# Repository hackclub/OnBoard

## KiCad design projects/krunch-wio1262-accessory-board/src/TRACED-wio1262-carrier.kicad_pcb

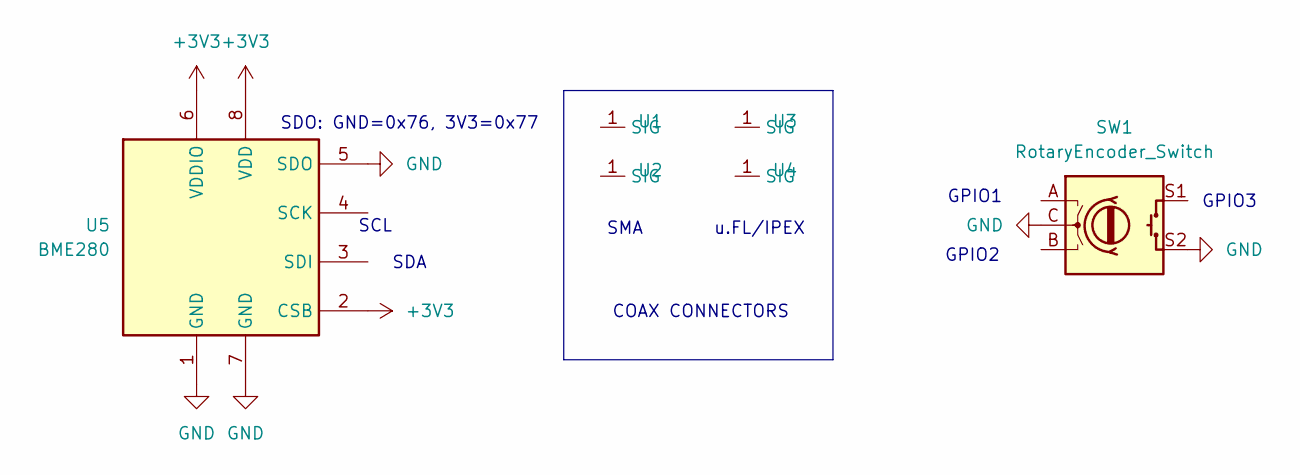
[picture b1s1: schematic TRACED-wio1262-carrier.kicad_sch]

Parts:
SW1: RotaryEncoder_Switch; RotaryEncoder_Alps_EC11E-Switch_Vertical_H20mm
U1, U2: SMA_BAT_Wireless_BWSMA-KWE-Z001; LCSC Part # C20617216
U3, U4: U.FL_Molex_MCRF_73412-0110_Vertical; LCSC Part # C434812
U5: BME280; Bosch_LGA-8_2.5x2.5mm_P0.65mm_ClockwisePinNumbering

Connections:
+3V3: U5.2 (CSB), U5.6 (VDDIO), U5.8 (VDD)
GND: SW1.C, SW1.S2, U5.1 (GND), U5.5 (SDO), U5.7 (GND)
GPIO1: SW1.A
GPIO2: SW1.B
GPIO3: SW1.S1
GPIO5/SDA: U5.3 (SDI)
GPIO6/SCL: U5.4 (SCK)

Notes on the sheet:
GPIO1
GPIO2
SMA
SCL
u.FL/IPEX
SDA
SDO: GND=0x76, 3V3=0x77
GPIO3
COAX CONNECTORS

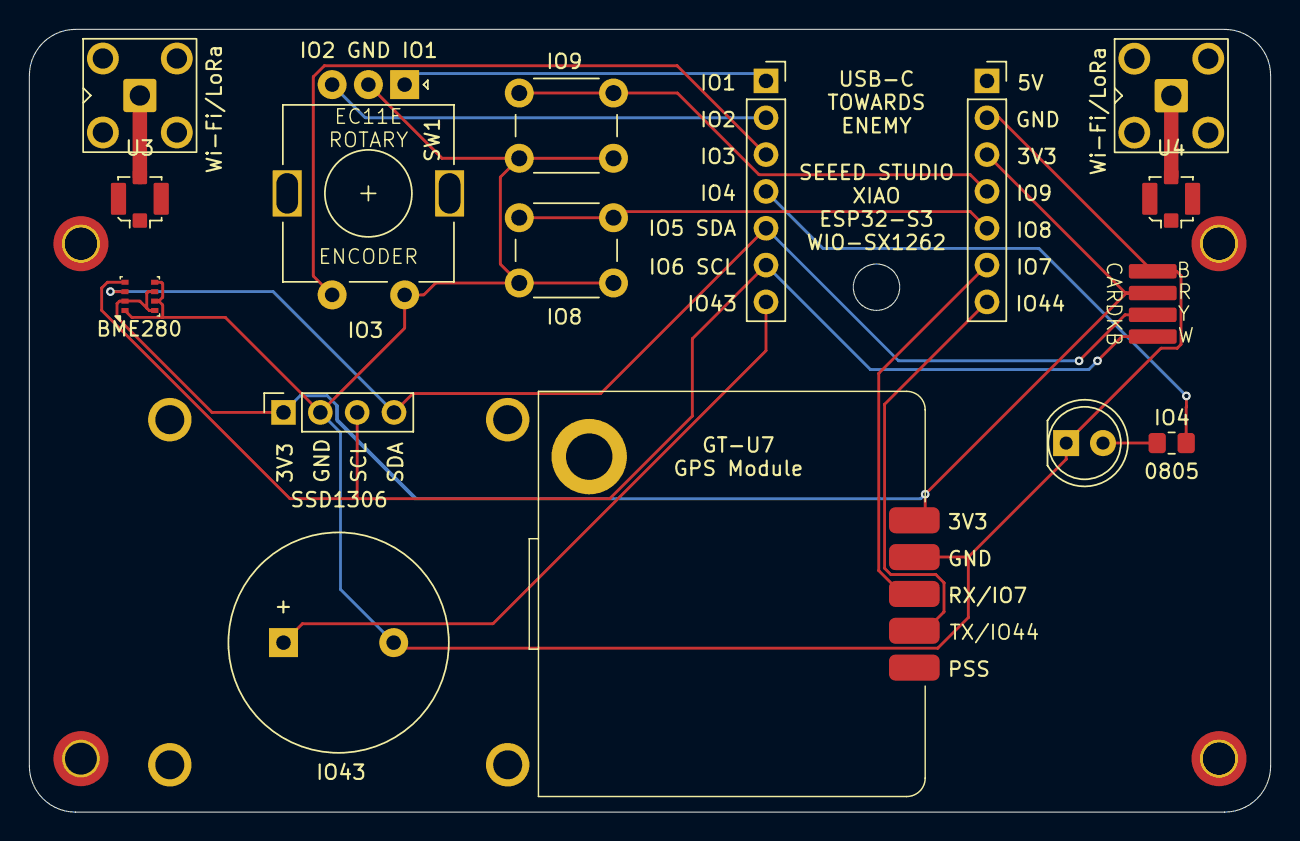
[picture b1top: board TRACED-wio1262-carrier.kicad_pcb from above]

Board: 2 copper layers, 85.6 x 54.0 mm, 6 parts (0 on the bottom side), 2 nets.

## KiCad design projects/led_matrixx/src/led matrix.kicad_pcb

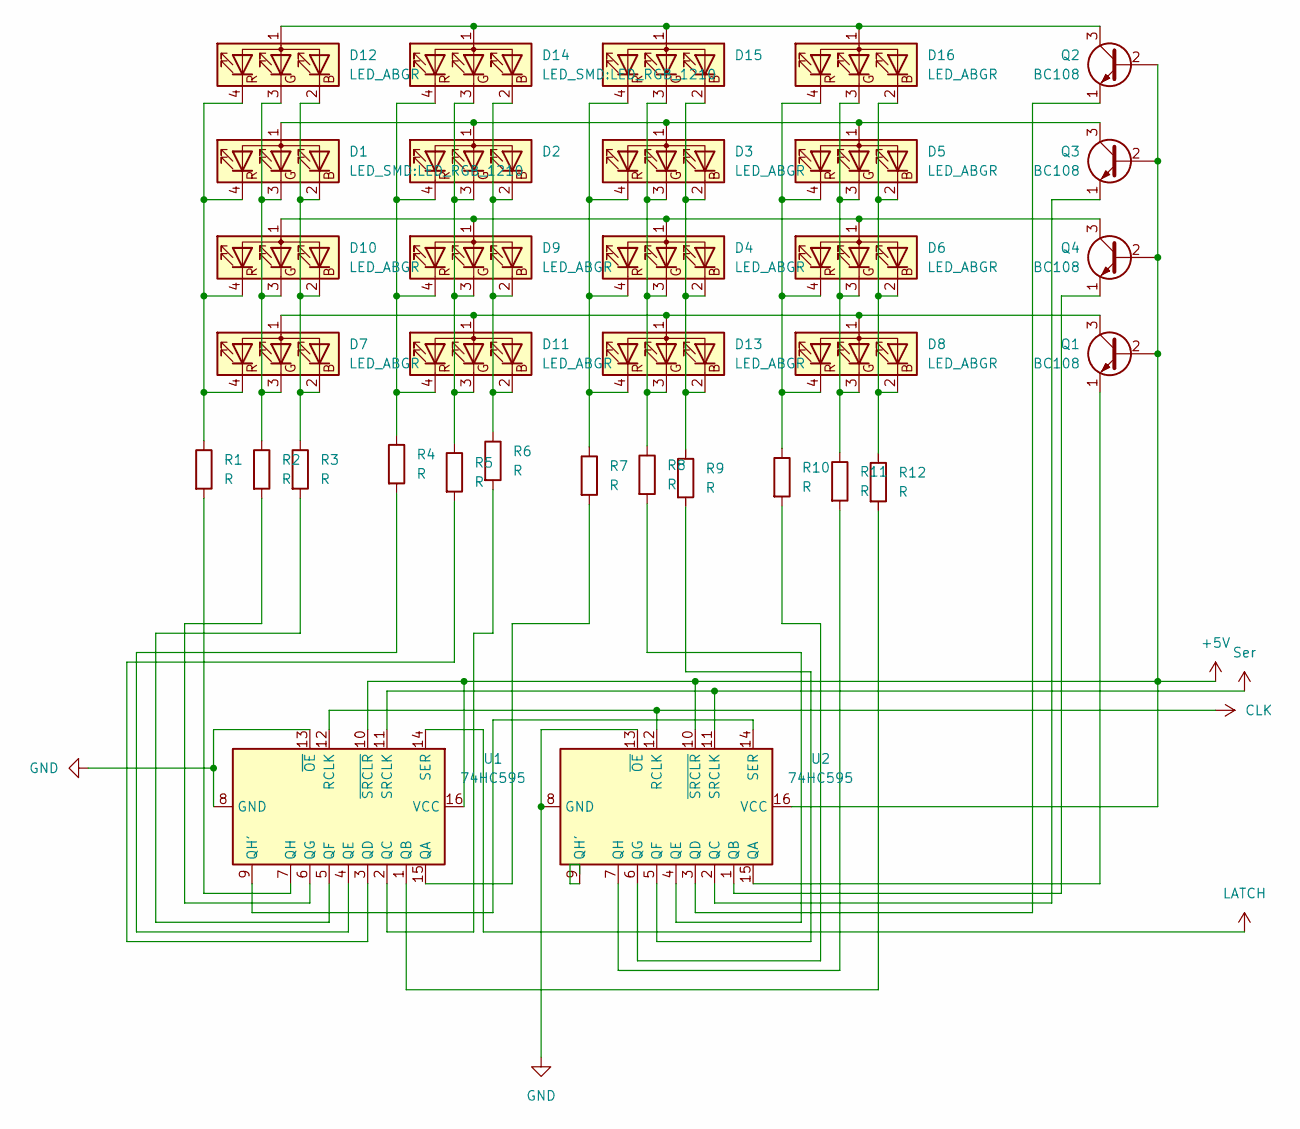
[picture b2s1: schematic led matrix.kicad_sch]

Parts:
D1, D14: LED_SMD:LED_RGB_1210; LED_RGB_1210
D2, D3, D4, D5, D6, D7, D8, D9, D10, D11, D12, D13, D15, D16: LED_ABGR; LED_RGB_1210
Q1, Q2, Q3, Q4: BC108; TO-18-3
R1, R2, R3, R4, R5, R6, R7, R8, R9, R10, R11, R12: R; R_0201_0603Metric
U1, U2: 74HC595; SSOP-16_5.3x6.2mm_P0.65mm

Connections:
+5V: Q1.2 (B), Q2.2 (B), Q3.2 (B), Q4.2 (B), U1.10 (~SRCLR), U1.16 (VCC), U2.10 (~SRCLR), U2.16 (VCC)
CLK: U1.12 (RCLK), U2.12 (RCLK)
GND: U1.8 (GND), U1.13 (~OE), U2.8 (GND), U2.13 (~OE)
LATCH: U1.14 (SER)
unnamed: D1.1 (A), D2.1 (A), D3.1 (A), D5.1 (A), Q3.3 (C)
unnamed: D1.2 (BK), D7.2 (BK), D10.2 (BK), D12.2 (BK), R3.1
unnamed: D1.3 (GK), D7.3 (GK), D10.3 (GK), D12.3 (GK), R2.1
unnamed: D1.4 (RK), D7.4 (RK), D10.4 (RK), D12.4 (RK), R1.1
unnamed: D4.1 (A), D6.1 (A), D9.1 (A), D10.1 (A), Q4.3 (C)
unnamed: D7.1 (A), D8.1 (A), D11.1 (A), D13.1 (A), Q1.3 (C)
unnamed: D2.2 (BK), D9.2 (BK), D11.2 (BK), D14.2 (BK), R6.1
unnamed: D2.3 (GK), D9.3 (GK), D11.3 (GK), D14.3 (GK), R5.1
unnamed: D2.4 (RK), D9.4 (RK), D11.4 (RK), D14.4 (RK), R4.1
unnamed: D12.1 (A), D14.1 (A), D15.1 (A), D16.1 (A), Q2.3 (C)
unnamed: D3.2 (BK), D4.2 (BK), D13.2 (BK), D15.2 (BK), R9.1
unnamed: D3.3 (GK), D4.3 (GK), D13.3 (GK), D15.3 (GK), R8.1
unnamed: D3.4 (RK), D4.4 (RK), D13.4 (RK), D15.4 (RK), R7.1
unnamed: D5.2 (BK), D6.2 (BK), D8.2 (BK), D16.2 (BK), R12.1
unnamed: D5.3 (GK), D6.3 (GK), D8.3 (GK), D16.3 (GK), R11.1
unnamed: D5.4 (RK), D6.4 (RK), D8.4 (RK), D16.4 (RK), R10.1
unnamed: Q1.1 (E), U2.15 (QA)
unnamed: Q2.1 (E), U2.3 (QD)
unnamed: Q3.1 (E), U2.2 (QC)
unnamed: Q4.1 (E), U2.1 (QB)
unnamed: R7.2, U1.15 (QA)
unnamed: R12.2, U1.1 (QB)
unnamed: R6.2, U1.2 (QC)
unnamed: R5.2, U1.3 (QD)
unnamed: R4.2, U1.4 (QE)
unnamed: R3.2, U1.5 (QF)
unnamed: R2.2, U1.6 (QG)
unnamed: U1.9 (QH'), U2.14 (SER)
unnamed: R1.2, U1.7 (QH)
unnamed: R8.2, U2.4 (QE)
unnamed: R9.2, U2.5 (QF)
unnamed: R10.2, U2.6 (QG)
unnamed: R11.2, U2.7 (QH)
Ser: U1.11 (SRCLK), U2.11 (SRCLK)

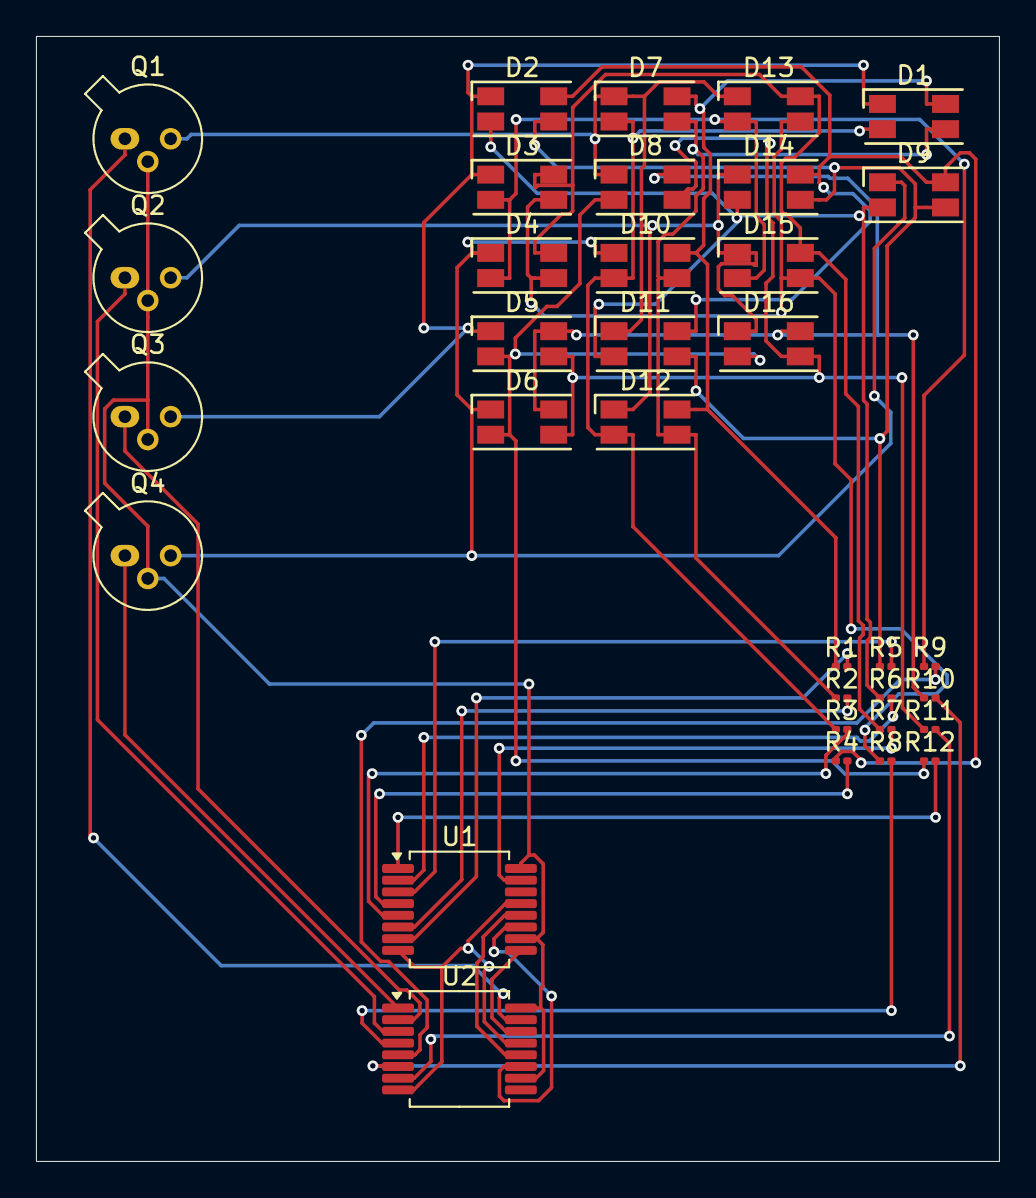
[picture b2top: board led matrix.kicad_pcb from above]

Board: 2 copper layers, 53.5 x 62.5 mm, 34 parts (0 on the bottom side), 37 nets.

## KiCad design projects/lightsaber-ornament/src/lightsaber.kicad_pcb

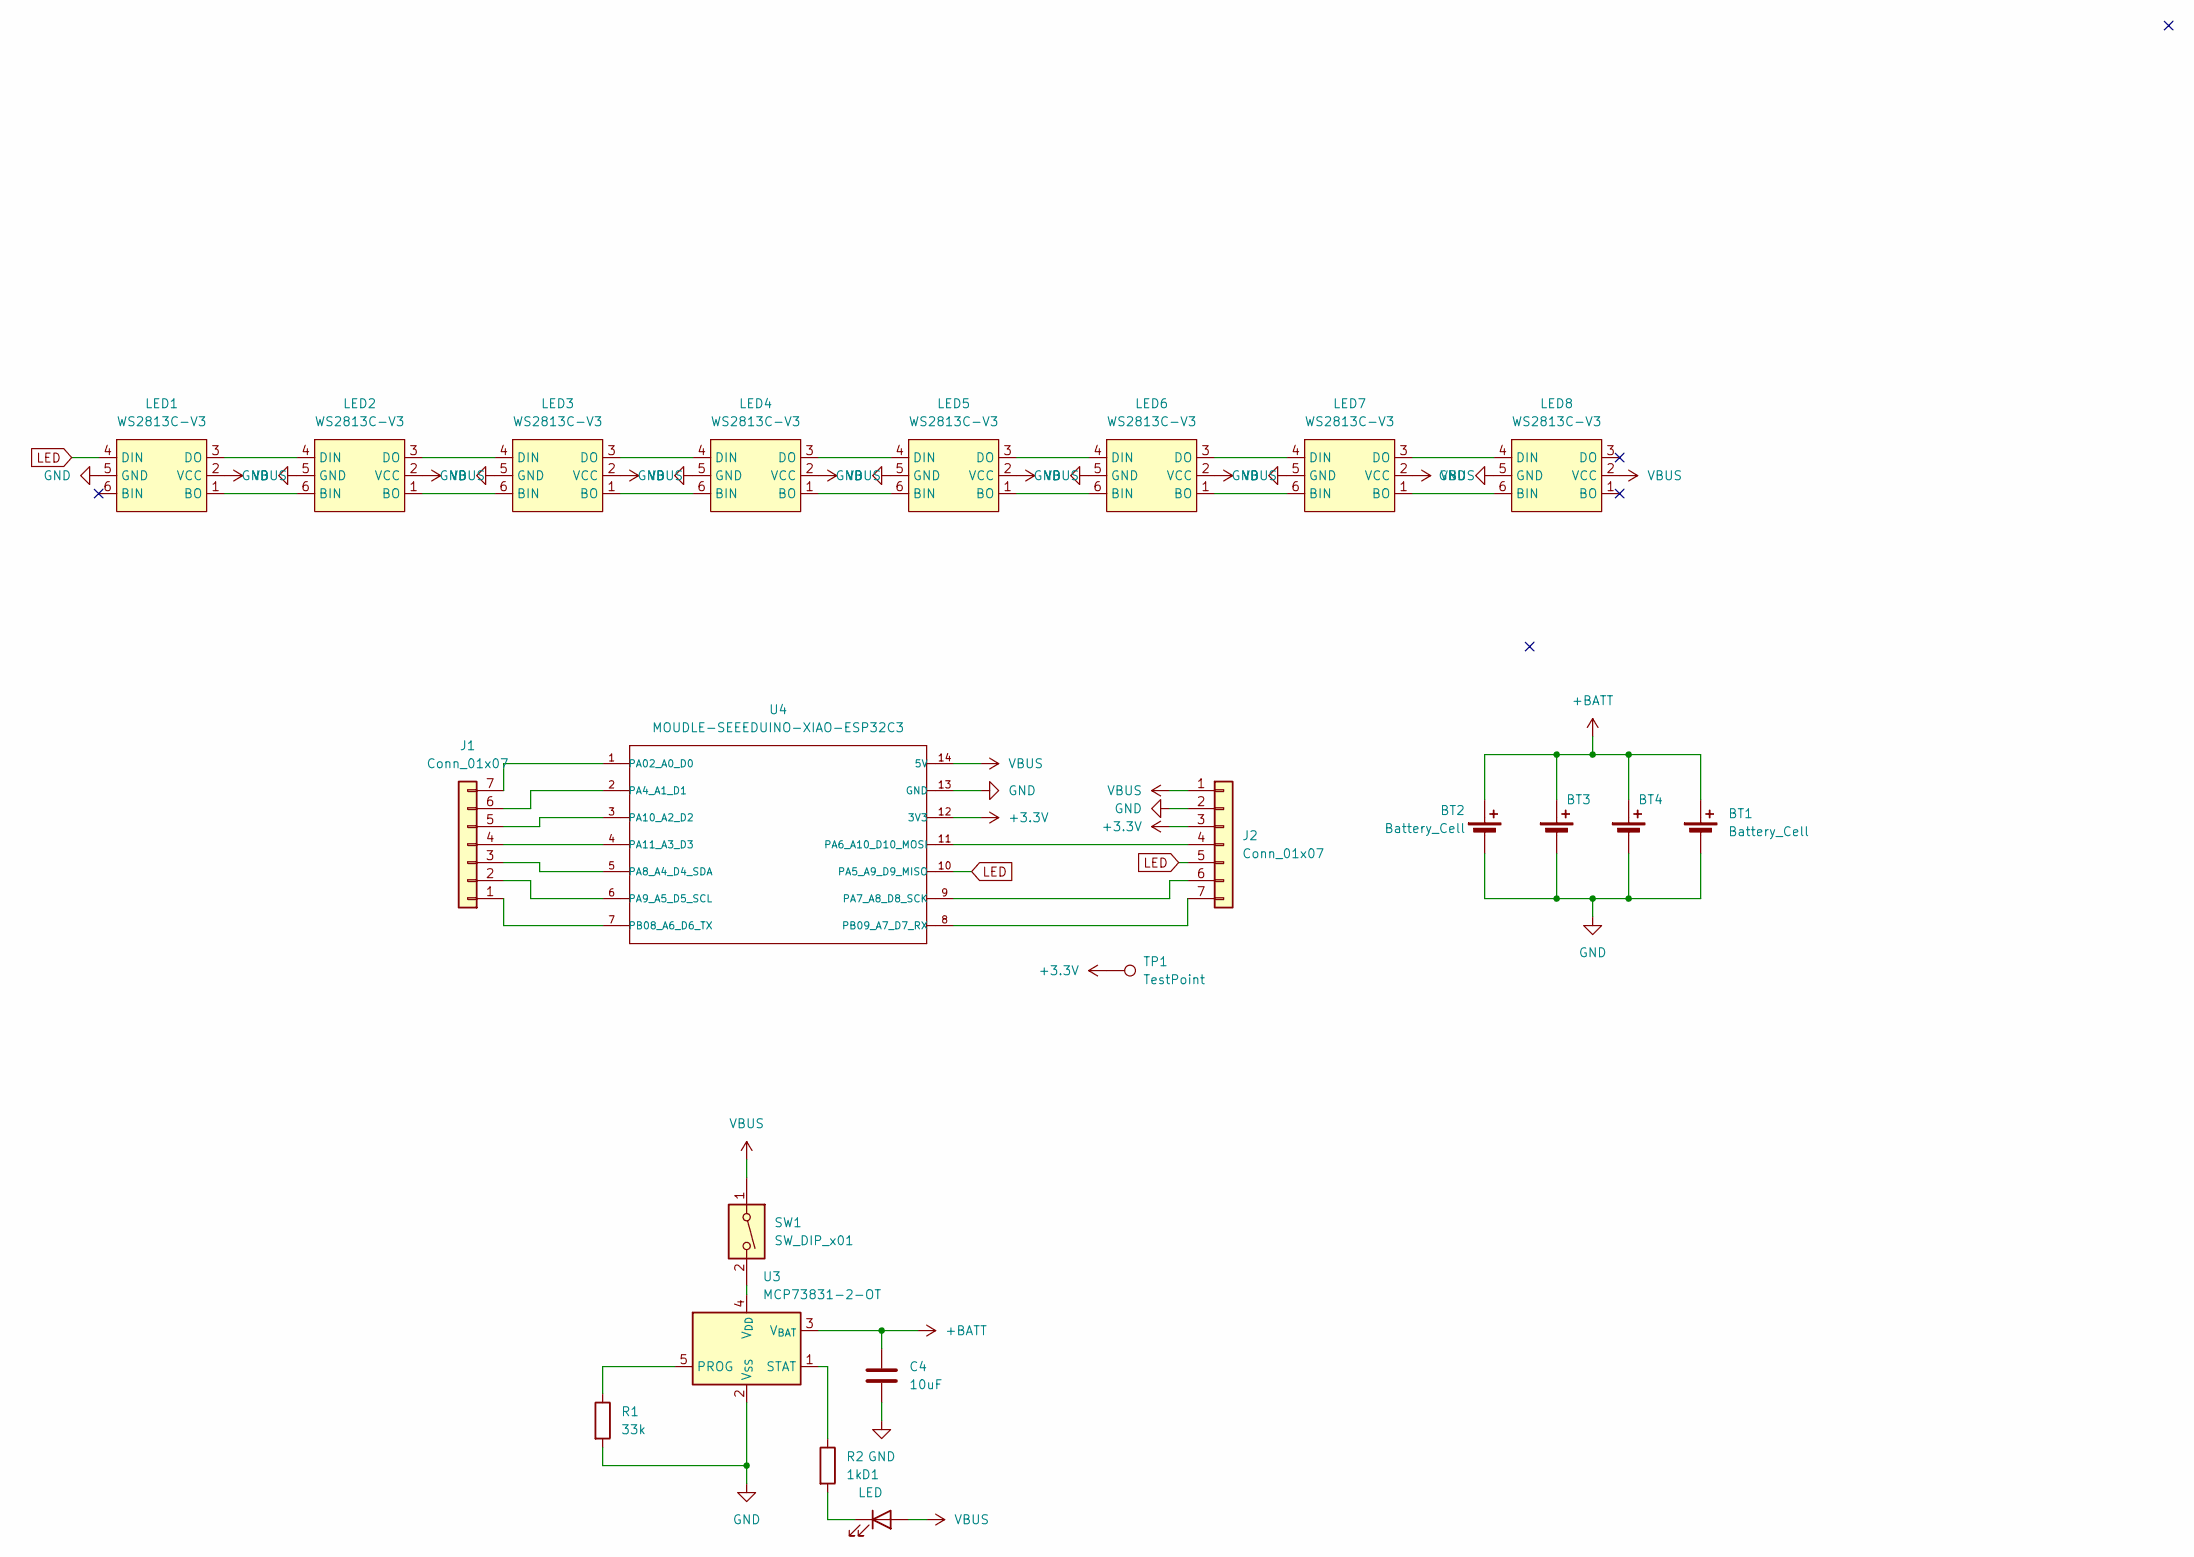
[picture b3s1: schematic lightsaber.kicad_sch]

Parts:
BT1, BT2, BT3, BT4: Battery_Cell; Battery_Panasonic_CR2032-HFN_Horizontal_CircularHoles
C4: 10uF; CAP_FA23_TDK
D1: LED; LED_D3.0mm_Clear
J1, J2: Conn_01x07; PinSocket_1x07_P2.54mm_Vertical
LED1, LED2, LED3, LED4, LED5, LED6, LED7, LED8: WS2813C-V3; LED-SMD_6P-L5.4-W5.0-BR_WS2813C-V3; LCSC Part C5359034
R1: 33k; R_0603_1608Metric_Pad0.98x0.95mm_HandSolder
R2: 1k; R_0603_1608Metric_Pad0.98x0.95mm_HandSolder
SW1: SW_DIP_x01; SW_DIP_SPSTx01_Piano_10.8x4.1mm_W7.62mm_P2.54mm
TP1: TestPoint; TestPoint_THTPad_D1.0mm_Drill0.5mm
U3: MCP73831-2-OT; SOT-23-5
U4: MOUDLE-SEEEDUINO-XIAO-ESP32C3; MOUDLE14P-SMD-2.54-21X17.8MM

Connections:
+3.3V: J2.3, TP1.1, U4.12 (3V3)
+BATT: BT1.1 (+), BT2.1 (+), BT3.1 (+), BT4.1 (+), C4.1, U3.3 (V_{BAT})
GND: BT1.2 (-), BT2.2 (-), BT3.2 (-), BT4.2 (-), C4.2, J2.2, LED1.5 (GND), LED2.5 (GND), LED3.5 (GND), LED4.5 (GND), LED5.5 (GND), LED6.5 (GND), LED7.5 (GND), LED8.5 (GND), R1.2, U3.2 (V_{SS}), U4.13 (GND)
LED: J2.5, LED1.4 (DIN), U4.10 (PA5_A9_D9_MISO)
unnamed: D1.1 (K), R2.2
unnamed: J1.1, U4.7 (PB08_A6_D6_TX)
unnamed: J1.2, U4.6 (PA9_A5_D5_SCL)
unnamed: J1.3, U4.5 (PA8_A4_D4_SDA)
unnamed: J1.4, U4.4 (PA11_A3_D3)
unnamed: J1.5, U4.3 (PA10_A2_D2)
unnamed: J1.6, U4.2 (PA4_A1_D1)
unnamed: J1.7, U4.1 (PA02_A0_D0)
unnamed: J2.4, U4.11 (PA6_A10_D10_MOSI)
unnamed: J2.6, U4.9 (PA7_A8_D8_SCK)
unnamed: J2.7, U4.8 (PB09_A7_D7_RX)
unnamed: LED1.1 (BO), LED2.6 (BIN)
unnamed: LED1.3 (DO), LED2.4 (DIN)
unnamed: LED2.1 (BO), LED3.6 (BIN)
unnamed: LED2.3 (DO), LED3.4 (DIN)
unnamed: LED3.1 (BO), LED4.6 (BIN)
unnamed: LED3.3 (DO), LED4.4 (DIN)
unnamed: LED4.1 (BO), LED5.6 (BIN)
unnamed: LED4.3 (DO), LED5.4 (DIN)
unnamed: LED5.1 (BO), LED6.6 (BIN)
unnamed: LED5.3 (DO), LED6.4 (DIN)
unnamed: LED6.1 (BO), LED7.6 (BIN)
unnamed: LED6.3 (DO), LED7.4 (DIN)
unnamed: LED7.1 (BO), LED8.6 (BIN)
unnamed: LED7.3 (DO), LED8.4 (DIN)
unnamed: R1.1, U3.5 (PROG)
unnamed: R2.1, U3.1 (STAT)
unnamed: SW1.2, U3.4 (V_{DD})
VBUS: D1.2 (A), J2.1, LED1.2 (VCC), LED2.2 (VCC), LED3.2 (VCC), LED4.2 (VCC), LED5.2 (VCC), LED6.2 (VCC), LED7.2 (VCC), LED8.2 (VCC), SW1.1, U4.14 (5V)

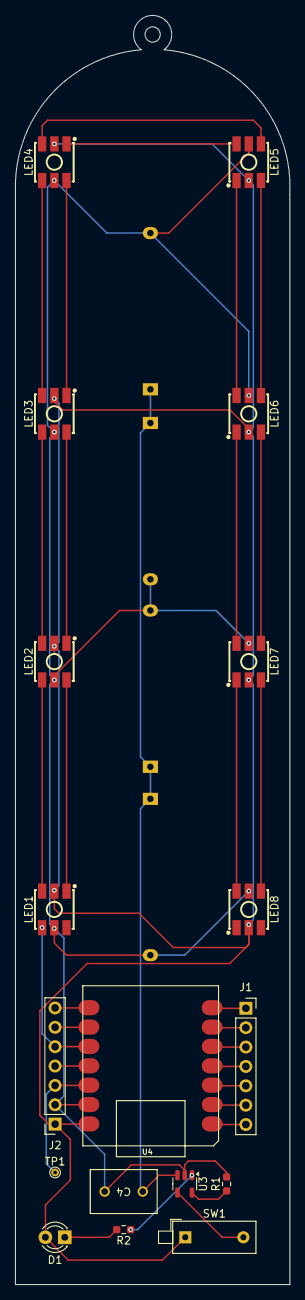
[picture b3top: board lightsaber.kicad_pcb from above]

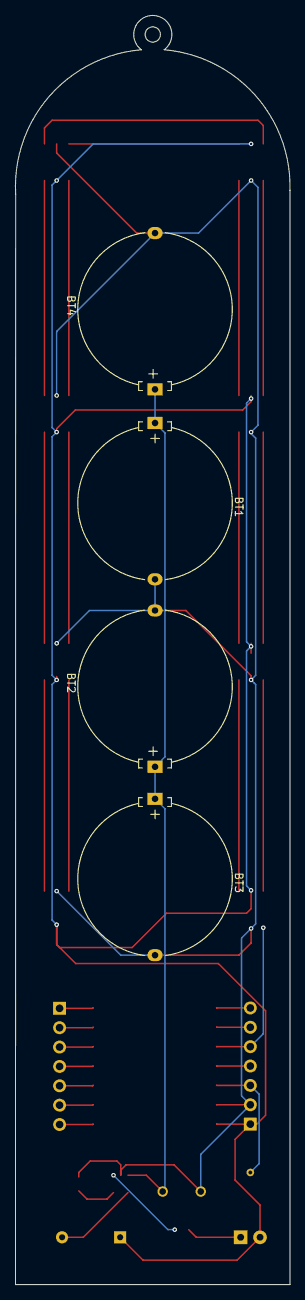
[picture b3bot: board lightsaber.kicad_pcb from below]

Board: 2 copper layers, 36.0 x 166.4 mm, 22 parts (4 on the bottom side), 33 nets.

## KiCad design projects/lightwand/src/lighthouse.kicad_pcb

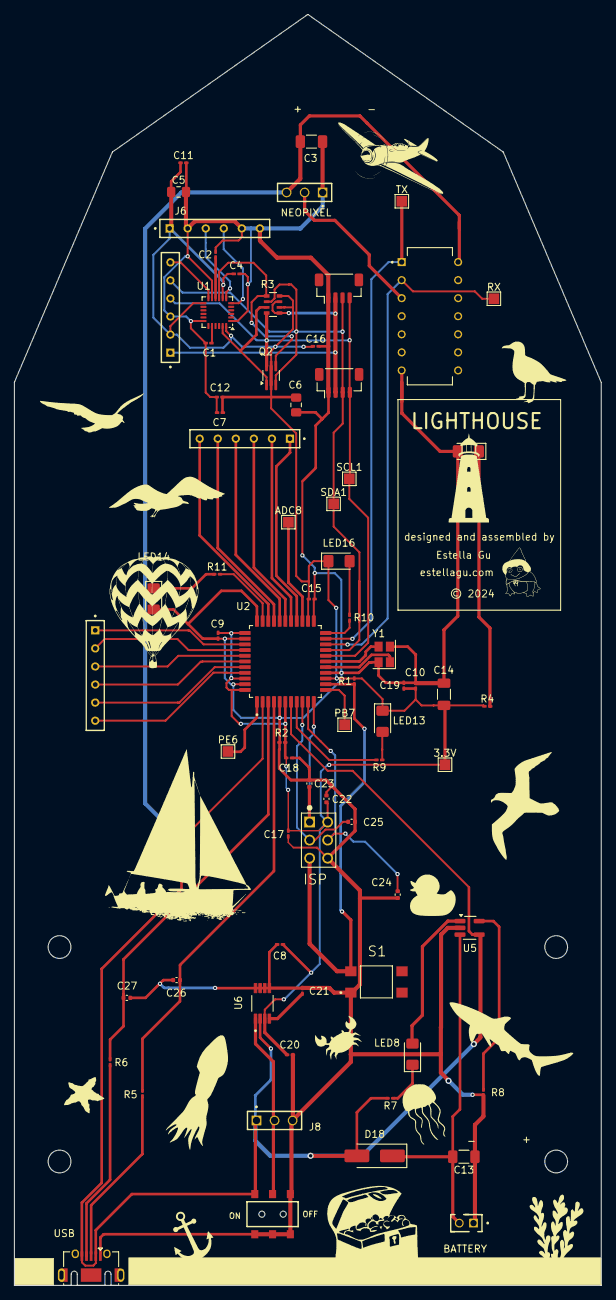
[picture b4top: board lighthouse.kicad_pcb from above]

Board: 2 copper layers, 82.5 x 178.8 mm, 76 parts (0 on the bottom side), 54 nets.

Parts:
3.3V: SEWTAP9; TestPoint_Pad_1.5x1.5mm
ADC8: SEWTAP9; TestPoint_Pad_1.5x1.5mm
BATTERY: MTMM-102-06-L-S-250
C1: 2.2nF; C_0201_0603Metric_Pad0.64x0.40mm_HandSolder
C2, C7, C8: 0.1uF; C_0201_0603Metric_Pad0.64x0.40mm_HandSolder
C3, C13, C14: 4.7uF; C_1206_3216Metric_Pad1.33x1.80mm_HandSolder
C4, C9, C12: .1uF; C_0201_0603Metric_Pad0.64x0.40mm_HandSolder
C5, C6: 10uF; C_0805_2012Metric_Pad1.18x1.45mm_HandSolder
C10, C11, C15, C16, C17, C19, C20: C-EUC0603; C_0201_0603Metric_Pad0.64x0.40mm_HandSolder
C18: 1uF; C_0201_0603Metric_Pad0.64x0.40mm_HandSolder
C21: 470pF; C_0201_0603Metric_Pad0.64x0.40mm_HandSolder
C22: 2.2uF; C_0402_1005Metric
C23, C24, C25, C26, C27: 10pF; C_0402_1005Metric
CONN3, CONN4: STEMMA_I2C_QT; JST_SH_BM04B-SRSS-TB_1x04-1MP_P1.00mm_Vertical
D18: DIODE-SCHOTTKY-B340A; D_SMA_Handsoldering
H1, H2, H3, H4: MountingHole; MountingHole_3.2mm_M3
ISP: 67997-206HLF
J3, J4, J5, J6: BBS-106-X-X
J8: TSW-101-23-L-T
LED1: GREEN; LED_1206_3216Metric_Pad1.42x1.75mm_HandSolder
LED8, LED13, LED14, LED16: RED; LED_1206_3216Metric_Pad1.42x1.75mm_HandSolder
NEOPIXEL: TSW-101-23-L-T
ON: SWITCH-DPDTAYZ0202; AYZ0202
PB7: SEWTAP9; TestPoint_Pad_1.5x1.5mm
PE6: SEWTAP9; TestPoint_Pad_1.5x1.5mm
Q2: BSS138; SOT-363_SC-70-6_Handsoldering
R1, R8: 10k; R_0201_0603Metric_Pad0.64x0.40mm_HandSolder
R2, R4: 10K; R_0201_0603Metric_Pad0.64x0.40mm_HandSolder
R3: 10K; R_Array_Convex_4x0603
R5, R6: 22; R_0201_0603Metric_Pad0.64x0.40mm_HandSolder
R7, R9, R10, R11: 330; R_0201_0603Metric_Pad0.64x0.40mm_HandSolder
RX: SEWTAP9; TestPoint_Pad_1.5x1.5mm
S1: TL3305BF160QG; SW_TL3305BF160QG
SCL1: SEWTAP9; TestPoint_Pad_1.5x1.5mm
SDA1: SEWTAP9; TestPoint_Pad_1.5x1.5mm
TX: SEWTAP9; TestPoint_Pad_1.5x1.5mm
U1: MPU-6050; InvenSense_QFN-24_4x4mm_P0.5mm
U2: ATMEGA32U41:1-LESS_PASTE; ATMEGA32U4-AUR
U5: MCP73831; SOT-23-5_HandSoldering
U6: MIC5219
U7: 74AHCT125; DIP794W45P254L1930H508Q14
USB: USB-ABCONN-11794; USB_Micro-AB_Molex_47590-0001
Y1: Crystal_GND24; Crystal_SMD_SeikoEpson_TSX3225-4Pin_3.2x2.5mm

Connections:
3.3V: 3.3V.1, C4.2, C5.1, C6.1, C7.1, C8.1, C9.2, C10.1, C11.1, C12.2, C14.2, C15.1, C16.1, C17.1, C18.2, C19.1, C20.1, C22.2, ISP.2, J5.02, J6.01, LED13.1 (A), LED16.1 (A), Q2.2 (G), Q2.5 (G), R1.1, R2.1, R3.2 (1), R3.4 (1), R4.1, U1.8 (VLOGIC), U1.13 (VDD), U1.24 (SDA), U2.6 (UCAP), U2.14 (VCC@14), U2.24 (AVCC@24), U2.34 (VCC@34), U2.42 (AREF), U2.44 (AVCC@44), U6.3 (OUT)
5V: C3.2, D18.2 (C), J8.01, NEOPIXEL.03, ON.1, R7.2, U2.2 (UVCC), U2.7 (VBUS), U5.4 (VIN), U6.2 (IN), USB.2 (D-), USB.5 (GND)
/CPOUT: C1.1, U1.20 (CPOUT)
/D+: C26.1, R5.1, U2.4 (D+)
/D-: C27.1, R6.1, U2.3 (D-)
/INT: J5.06, U1.12 (INT)
/REGOUT: C2.1, U1.10 (REGOUT)
/RX_LED: R9.2, U2.8 (PB0(SS))
/SCL: CONN3.4 (SCL), CONN4.4 (SCL), J5.04, Q2.6 (D), R3.8 (2), SCL1.1, U2.18 (PD0(SCL))
/SCL_3V: Q2.1 (S), R3.7 (2), U1.23 (SCL)
/SCL_EXT: J6.03, U1.7 (AUX_CL)
/SDA: CONN3.3 (SDA), CONN4.3 (SDA), J5.05, Q2.3 (D), R3.6 (2), SDA1.1, U2.19 (PD1(SDA))
/SDA_3V: Q2.4 (S), R3.5 (2), U1.9 (AD0)
/SDA_EXT: J6.04, U1.6 (AUX_DA)
/TX_LED: R10.2, U2.22 (PD5)
/USER_LED: R11.2, U2.32 (PC7)
GND: BATTERY.01, C1.2, C2.2, C3.1, C4.1, C5.2, C6.2, C7.2, C8.2, C9.1, C10.2, C11.2, C12.1, C13.1, C14.1, C15.2, C16.2, C17.2, C18.1, C19.2, C20.2, C21.1, C22.1, C23.2, C24.2, C25.1, C26.2, C27.2, CONN3.1 (GND), CONN4.1 (GND), ISP.6, J5.03, J6.02, J6.05, J6.06, J8.03, LED1.2 (C), LED14.2 (C), NEOPIXEL.01, ON.3, ON.4, ON.5, ON.6, R2.2, R8.1, S1.1, U1.1 (CLKIN), U1.11 (FSYNC), U1.18 (GND), U2.5 (UGND), U2.15 (GND@15), U2.23 (GND@23), U2.33 (PE2/~HWB), U2.35 (GND@35), U2.43 (GND@43), U5.2 (VSS), U6.5 (GND), U6.6 (GND), U6.7 (GND), U6.8 (GND), USB.1 (VBUS), Y1.2, Y1.4
unnamed: LED1.1 (A), R4.2
unnamed: LED8.1 (A), R7.1
unnamed: LED8.2 (C), U5.1 (STAT)
unnamed: LED13.2 (C), R9.1
unnamed: LED14.1 (A), R11.1
unnamed: LED16.2 (C), R10.1
unnamed: NEOPIXEL.02, U7.3
unnamed: ISP.5, R1.2, S1.3 (2), U2.13 (~RESET)
unnamed: C25.2, ISP.3, U2.9 (PB1(SCK))
unnamed: C24.1, ISP.4, U2.10 (PB2(MOSI))
unnamed: C23.1, ISP.1, U2.11 (PB3(MISO))
unnamed: J4.03, U2.28 (PB4(ADC11))
unnamed: J4.04, U2.29 (PB5(ADC12))
unnamed: J4.05, U2.30 (PB6(ADC13))
unnamed: PB7.1, U2.12 (PB7)
unnamed: J4.06, U2.31 (PC6)
unnamed: RX.1, U2.20 (PD2(RX)), U7.2
unnamed: TX.1, U2.21 (PD3(TX)), U7.1
unnamed: ADC8.1, U2.25 (PD4(ADC8))
unnamed: J4.01, U2.26 (PD6(ADC9))
unnamed: J4.02, U2.27 (PD7(ADC10))
unnamed: PE6.1, U2.1 (PE6)
unnamed: J3.06, U2.41 (PF0(ADC0))
unnamed: J3.05, U2.40 (PF1(ADC1))
unnamed: J3.04, U2.39 (PF4(ADC4))
unnamed: J3.03, U2.38 (PF5(ADC5))
unnamed: J3.02, U2.37 (PF6(ADC6))
unnamed: J3.01, U2.36 (PF7(ADC7))
unnamed: U2.17 (XTAL1), Y1.3
unnamed: U2.16 (XTAL2), Y1.1
unnamed: R8.2, U5.5 (PROG)
unnamed: C21.2, U6.4 (BYP)
unnamed: J8.02, ON.2, U6.1 (EN)
unnamed: R5.2, USB.3 (D+)
unnamed: R6.2, USB.4 (USBID)
VCC: CONN3.2 (V+), CONN4.2 (V+), J5.01, R3.1, R3.3 (1)
V_BATT: BATTERY.02, C13.2, D18.1 (A), U5.3 (VBAT)

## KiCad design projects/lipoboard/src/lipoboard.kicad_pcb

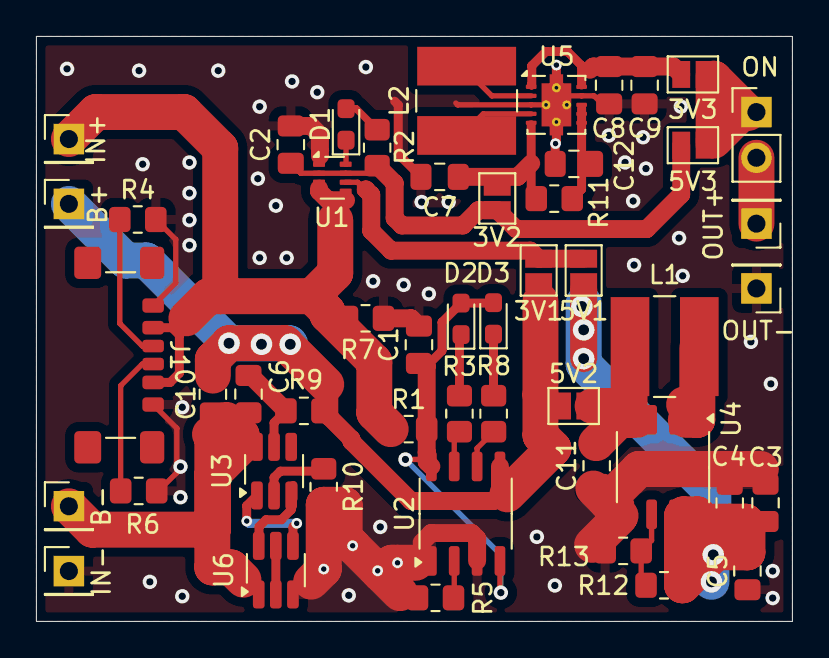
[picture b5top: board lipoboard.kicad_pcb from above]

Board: 2 copper layers, 42.0 x 32.5 mm, 50 parts (0 on the bottom side), 32 nets.

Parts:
3V1, 3V2, 3V3, 5V1, 5V2, 5V3: Jumper_2_Open; SolderJumper-2_P1.3mm_Open_Pad1.0x1.5mm
B+: Conn_01x01_Pin; PinHeader_1x01_P2.54mm_Vertical
B-: Conn_01x01_Pin; PinHeader_1x01_P2.54mm_Vertical
C1, C2, C3, C4, C5, C7, C8, C9, C10: 10uF; C_0805_2012Metric_Pad1.18x1.45mm_HandSolder
C6, C12: 0.1uF; C_0805_2012Metric_Pad1.18x1.45mm_HandSolder
C11: 22uF; C_0805_2012Metric_Pad1.18x1.45mm_HandSolder
D1, D3: GLED; LED_0603_1608Metric_Pad1.05x0.95mm_HandSolder
D2: RLED; LED_0603_1608Metric_Pad1.05x0.95mm_HandSolder
IN+: Conn_01x01_Pin; PinHeader_1x01_P2.54mm_Vertical
IN-: Conn_01x01_Pin; PinHeader_1x01_P2.54mm_Vertical
J1: USB_C_Receptacle_PowerOnly_24P; USB_C_Receptacle_GCT_USB4135-GF-A_6P_TopMnt_Horizontal
L1, L2: 2.2uH; L_TracoPower_TCK-047_5.2x5.8mm
ON: SW_DIP_x01; PinHeader_1x02_P2.54mm_Vertical
OUT+: Conn_01x01_Pin; PinHeader_1x01_P2.54mm_Vertical
OUT-: Conn_01x01_Pin; PinHeader_1x01_P2.54mm_Vertical
R1: 0.4Ω; R_0805_2012Metric_Pad1.20x1.40mm_HandSolder
R2, R3, R8: 1kΩ; R_0805_2012Metric_Pad1.20x1.40mm_HandSolder
R4, R6: 5.1kΩ; R_0805_2012Metric_Pad1.20x1.40mm_HandSolder
R5: 1.33kΩ; R_0805_2012Metric_Pad1.20x1.40mm_HandSolder
R7: 10kΩ; R_0805_2012Metric_Pad1.20x1.40mm_HandSolder
R9: 470Ω; R_0805_2012Metric_Pad1.20x1.40mm_HandSolder
R10: 2kΩ; R_0805_2012Metric_Pad1.20x1.40mm_HandSolder
R11: 100Ω; R_0805_2012Metric_Pad1.20x1.40mm_HandSolder
R12: 300kΩ; R_0805_2012Metric_Pad1.20x1.40mm_HandSolder
R13: 75kΩ; R_0805_2012Metric_Pad1.20x1.40mm_HandSolder
U1: TPS2116DRL; SOT-583-8
U2: TP4056; SOP-8_3.9x4.9mm_P1.27mm
U3: DW01A; SOT-23-6_Handsoldering
U4: TP5188; SOP-8_3.9x4.9mm_P1.27mm
U5: TPS63001; Texas_DRC0010J_ThermalVias
U6: 8025A; SOT-23-6_Handsoldering

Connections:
3.3VOUT: 3V3.1 (A), C8.1, C9.1, U5.1 (VOUT), U5.10 (FB)
5VOUT: 5V1.1 (A), C3.1, C4.1, C5.1, R12.1, U4.7 (VOUT), U4.8 (VOUT)
GND: C1.2, C2.2, C3.2, C4.2, C5.2, C7.2, C8.2, C9.2, C11.2, C12.2, IN-.1, J1.A12 (GND), J1.B12 (GND), OUT-.1, R4.2, R5.2, R6.2, R7.1, R10.2, R13.1, U1.1 (GND), U2.1 (TEMP), U2.3 (GND), U4.5 (GND), U5.3 (PGND), U5.9 (GND), U5.11 (PGND), U6.3 (S2)
MUXOUT: 3V2.2 (B), 5V3.1 (A), C2.1, R2.2, U1.2 (VOUT), U1.7 (VOUT)
unnamed: 3V1.2 (B), 5V1.2 (B), U1.6 (VIN2)
unnamed: 3V2.1 (A), C7.1, R11.2, U5.5 (VIN)
unnamed: 3V3.2 (B), 5V3.2 (B), ON.1
unnamed: 5V2.2 (B), C11.1, L1.1, U4.3 (BAT), U4.4 (EN)
unnamed: B-.1, C6.2, C10.2, U3.6 (GND), U6.1 (S1)
unnamed: D1.2 (A), R2.1
unnamed: D1.1 (K), U1.8 (ST)
unnamed: D2.1 (K), R3.1
unnamed: D3.1 (K), R8.1
unnamed: J1.A5 (CC1), R4.1
unnamed: J1.B5 (CC2), R6.1
unnamed: L1.2, U4.1 (SW), U4.2 (SW)
unnamed: ON.2, OUT+.1
unnamed: R5.1, U2.2 (PROG)
unnamed: R3.2, U2.7 (~CHRG)
unnamed: R8.2, U2.6 (~STDBY)
unnamed: R10.1, U3.2 (CS)
unnamed: U3.3 (OC), U6.6 (G2)
unnamed: U3.1 (OD), U6.4 (G1)
unnamed: C6.1, R9.2, U3.5 (VCC)
unnamed: R12.2, R13.2, U4.6 (FB)
unnamed: C12.1, R11.1, U5.6 (EN), U5.7 (PS/SYNC), U5.8 (VINA)
unnamed: L2.2, U5.4 (L1)
unnamed: L2.1, U5.2 (L2)
unnamed: U6.2 (D1), U6.5 (D2)
VBAT: 3V1.1 (A), 5V2.1 (A), B+.1, C10.1, R9.1, U2.5 (BAT)
VBUS: IN+.1, J1.A9 (VBUS), J1.B9 (VBUS), R1.1, R7.2, U1.3 (VIN1), U1.4 (PR1), U1.5 (MODE)
VCRG: C1.1, D2.2 (A), D3.2 (A), R1.2, U2.4 (VCC), U2.8 (CE)

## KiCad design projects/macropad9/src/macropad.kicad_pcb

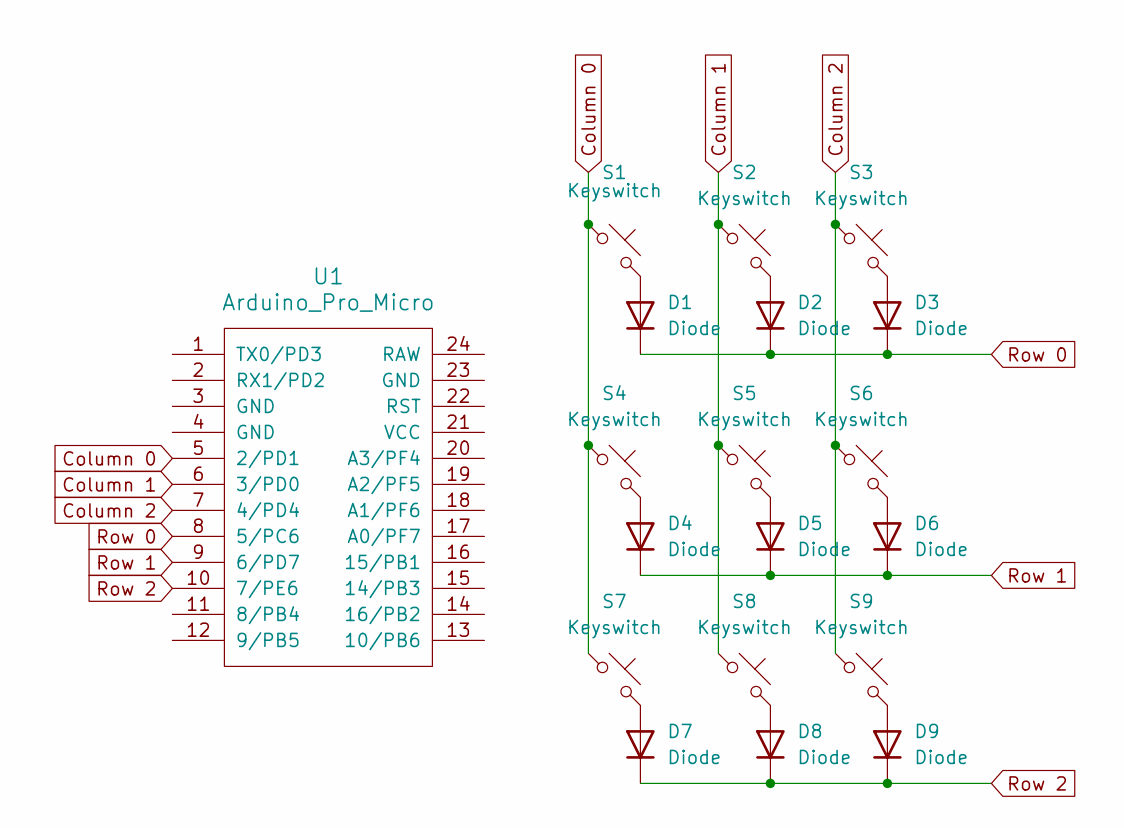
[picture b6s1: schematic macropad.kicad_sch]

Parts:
D1, D2, D3, D4, D5, D6, D7, D8, D9: Diode; Diode_DO-35
S1, S2, S3, S4, S5, S6, S7, S8, S9: Keyswitch; MX_Plate_1.00u
U1: Arduino_Pro_Micro

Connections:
Column 0: S1.1, S4.1, S7.1, U1.5 (2/PD1)
Column 1: S2.1, S5.1, S8.1, U1.6 (3/PD0)
Column 2: S3.1, S6.1, S9.1, U1.7 (4/PD4)
unnamed: D1.2 (A), S1.2
unnamed: D2.2 (A), S2.2
unnamed: D3.2 (A), S3.2
unnamed: D4.2 (A), S4.2
unnamed: D5.2 (A), S5.2
unnamed: D6.2 (A), S6.2
unnamed: D7.2 (A), S7.2
unnamed: D8.2 (A), S8.2
unnamed: D9.2 (A), S9.2
Row 0: D1.1 (K), D2.1 (K), D3.1 (K), U1.8 (5/PC6)
Row 1: D4.1 (K), D5.1 (K), D6.1 (K), U1.9 (6/PD7)
Row 2: D7.1 (K), D8.1 (K), D9.1 (K), U1.10 (7/PE6)

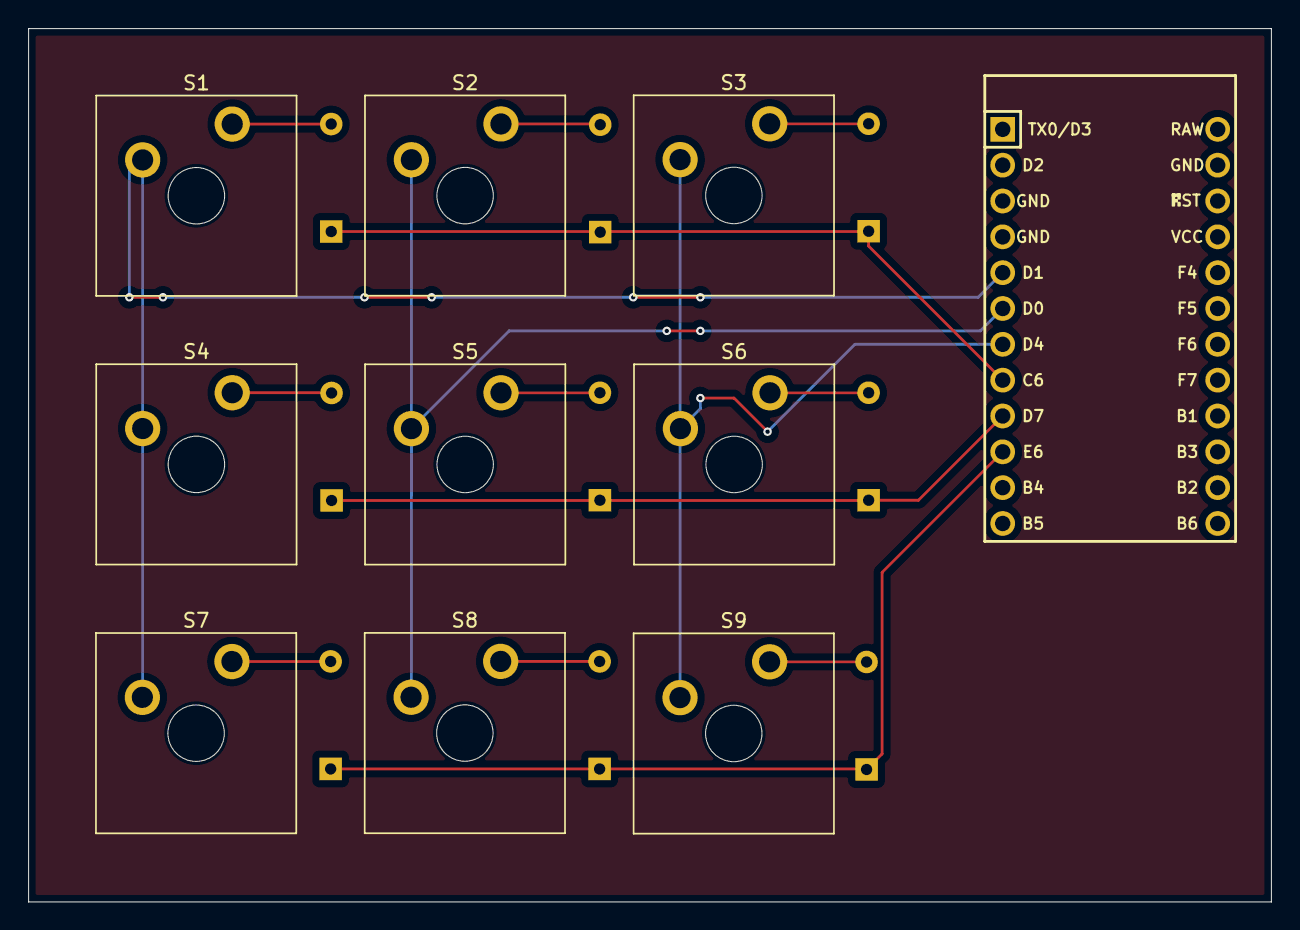
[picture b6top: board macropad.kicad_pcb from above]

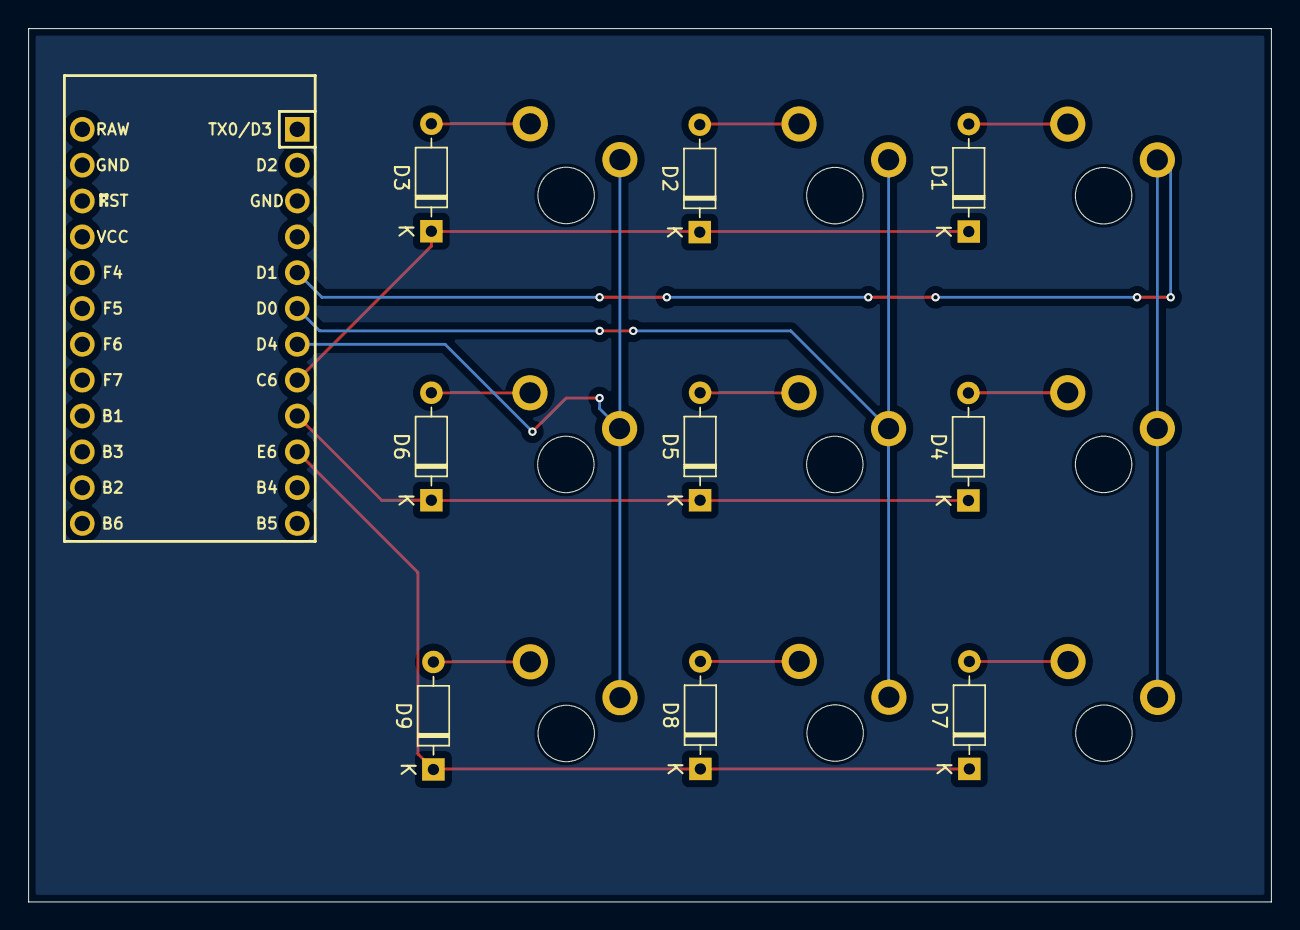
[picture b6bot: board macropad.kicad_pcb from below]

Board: 2 copper layers, 88.1 x 61.9 mm, 19 parts (9 on the bottom side), 15 nets.

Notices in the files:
projects/lightwand/src/lighthouse.kicad_pcb:
© 2024
